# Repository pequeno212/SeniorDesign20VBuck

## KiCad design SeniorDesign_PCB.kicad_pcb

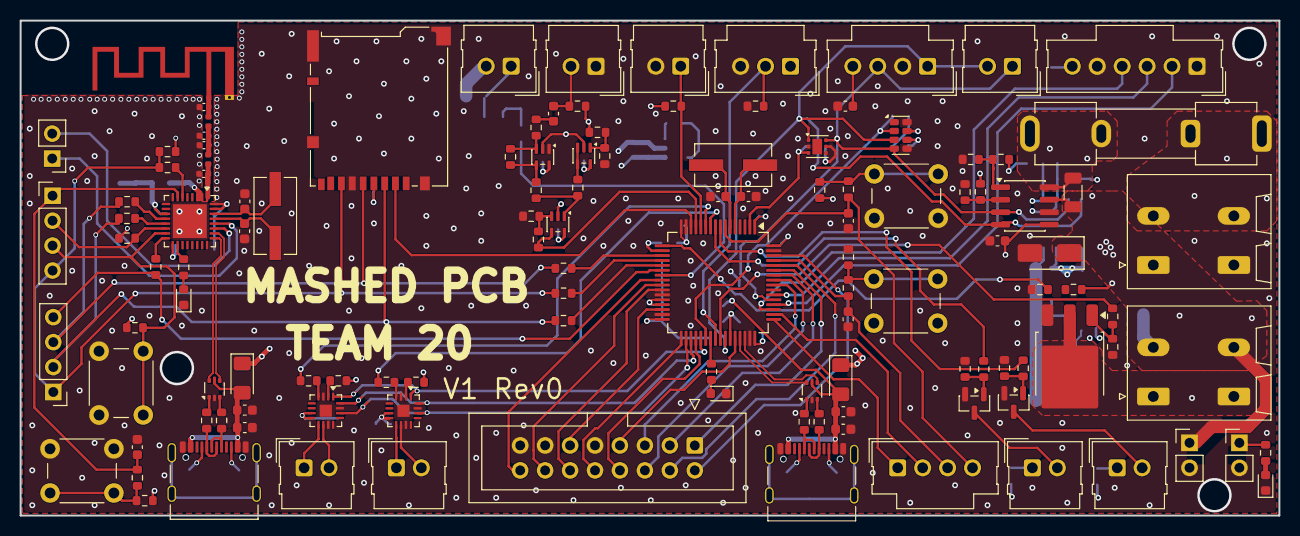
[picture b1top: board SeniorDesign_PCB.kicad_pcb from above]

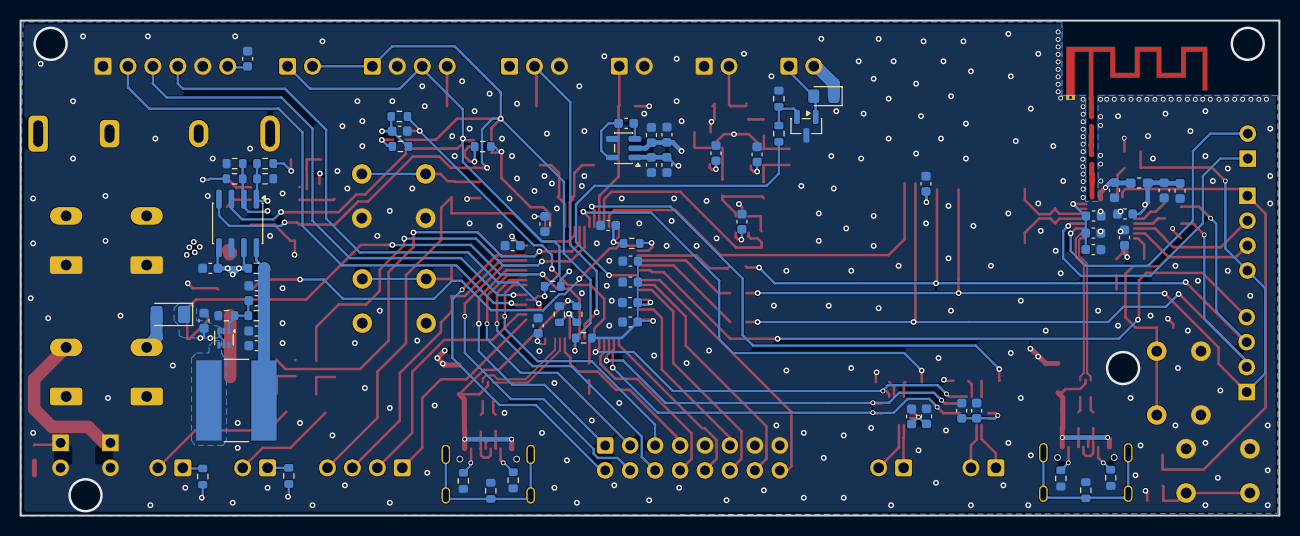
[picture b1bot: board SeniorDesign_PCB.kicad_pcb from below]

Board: 4 copper layers, 128.2 x 50.4 mm, 193 parts (70 on the bottom side), 135 nets.

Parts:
AE1: Antenna_Shield; Texas_SWRA117D_2.4GHz_Left
C1, C22, C23, C33, C39, C43, C48, C49: 1u; C_0603_1608Metric
C2, C3, C4, C5, C6, C7, C10, C11, C13, C14, C17, C18, C19, C24, C25, C32, C34, C35, C36, C37, C40, C41, C42, C44, C45, C46, C47, C50, C52, C53: 100n; C_0603_1608Metric
C8, C9, C26, C27: 22p; C_0603_1608Metric
C12, C16, C38: 10u; C_0603_1608Metric
C15: 1uF; C_0603_1608Metric
C20: 4u7; C_0603_1608Metric
C21: 22u; C_0603_1608Metric
C28, C29, C30, C31: DNP; C_0402_1005Metric
C51, C54, C55: DNP; C_0603_1608Metric
D2, D5, D9: LED; LED_0603_1608Metric
D4: SMAJ5.0A; D_SMA
D6, D7: D; D_1206_3216Metric_Pad1.42x1.75mm_HandSolder
D8: D; D_0805_2012Metric_Pad1.15x1.40mm_HandSolder
D10: D; D_1206_3216Metric
F1: RGEF1400; Fuseholder_Clip-5x20mm_Keystone_3512P_Inline_P23.62x7.27mm_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
J1, J4: Conn_01x04_Pin; Molex_SL_171971-0004_1x04_P2.54mm_Vertical
J2, J6, J7, J8, J19, J20: Conn_01x02_Socket; Molex_SL_171971-0002_1x02_P2.54mm_Vertical
J3: Conn_01x03_Socket; Molex_SL_171971-0003_1x03_P2.54mm_Vertical
J5, J15: Conn_01x02_Pin; Molex_SL_171971-0002_1x02_P2.54mm_Vertical
J10, J24: Conn_01x02_Socket; PhoenixContact_SPT_2.5_2-H-5.0_1x02_P5.0mm_Horizontal
J11: Conn_01x02_Pin; PinHeader_1x02_P2.54mm_Vertical
J12, J13: USB_C_Receptacle_USB2.0_14P; USB_C_Receptacle_Palconn_UTC16-G
J14: IDC_Cable_02x08; IDC-Header_2x08_P2.54mm_Vertical
J16, J17: Conn_01x04_Pin; PinHeader_1x04_P2.54mm_Vertical
J18: Micro_SD_Card; microSD_HC_Hirose_DM3BT-DSF-PEJS
J21: MIC_I2S_CONNECTOR; Molex_SL_171971-0006_1x06_P2.54mm_Vertical
J22, J23: Conn_01x02_Socket; PinHeader_1x02_P2.54mm_Vertical
L1: 1u; L_Bourns-SRN8040_8x8.15mm
L2, L3: DNP; L_0402_1005Metric
L4: 2n; L_0603_1608Metric_Pad1.05x0.95mm_HandSolder
Q1: NMOS; TO-252-3_TabPin2
Q2: NMOS; SOT-23
Q4, Q5: AO3400A; SOT-23
R2, R7, R8, R10, R15, R17, R18, R24, R25, R32, R38, R39, R53, R59, R60, R78, R79, R81, R84: 10k; R_0603_1608Metric
R3, R21: 2k2; R_0603_1608Metric
R5, R6, R44, R45, R46, R47: 5k1; R_0603_1608Metric
R9: 7k; R_0603_1608Metric
R11, R43, R54: 330; R_0603_1608Metric
R12, R13, R14, R20, R34, R35, R55, R56, R57, R58, R69, R70, R73, R75: 0R; R_0603_1608Metric
R19, R22, R26, R27, R28, R29, R37, R76: 1k; R_0603_1608Metric
R23: 18k; R_0603_1608Metric
R30: 210k; R_0603_1608Metric
R31, R52: 10R; R_0603_1608Metric
R33: 2m; R_1206_3216Metric
R36, R41: 100k; R_0603_1608Metric
R40: 453k; R_0603_1608Metric
R42: 2m; R_0603_1608Metric
R48, R49, R50, R51: 22R; R_0603_1608Metric
R61, R62, R68, R71, R72, R74: DNP; R_0603_1608Metric
R80, R83: 10; R_0603_1608Metric
R82, R85: 17; R_0603_1608Metric
SW2, SW5, SW6, SW7: SW_Push; SW_PUSH_6mm
U1: TMP117xxDRV; WSON-6-1EP_2x2mm_P0.65mm_EP1x1.6mm
U2: RV-3028-C7; MicroCrystal_C7_SON-8_1.5x3.2mm_P0.9mm
U3: STM32G474RETx; LQFP-64_10x10mm_P0.5mm
U5, U8: MAX98357A; TQFN-16-1EP_3x3mm_P0.5mm_EP1.23x1.23mm
U6, U7, U16: TLV172IDCK; SOT-353_SC-70-5
U9, U10: INA219AxD; SOIC-8_3.9x4.9mm_P1.27mm
U11: TLV62569ADRL; SOT-563
U12, U13: USBLC6-2P6; SOT-666
U14: ESP32-C3FH4; QFN-32-1EP_5x5mm_P0.5mm_EP3.45x3.45mm
U15: TPS60400DBV; SOT-23-5
Y1: 16MHz; Crystal_SMD_ECS_CSM3X-2Pin_7.6x4.1mm
Y2: 40MHz; Crystal_SMD_ECS_CSM3X-2Pin_7.6x4.1mm

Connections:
3V3: C1.1, C2.1, C3.1, C4.1, C5.1, C6.1, C7.1, C10.1, C12.1, C13.1, C14.1, C16.1, C17.1, C18.1, C19.1, C32.1, C34.1, C35.1, C36.1, C37.1, C38.1, C39.1, C40.1, C41.1, C44.1, C46.1, C47.1, C48.1, C52.1, C53.1, J1.4, J3.1, J18.4 (VDD), J21.6, J22.1, L4.2, R2.1, R3.1, R5.2, R6.2, R7.1, R8.1, R15.1, R18.1, R21.1, R24.2, R34.1, R35.1, R42.2, R43.1, R59.1, R60.1, R68.2, R69.2, R72.2, R74.2, R78.1, R79.1, R82.1, R85.1, SW2.2, U1.5 (V+), U2.7 (VDD), U3.1 (VBAT), U3.16 (VDD), U3.28 (VREF+), U3.29 (VDDA), U3.32 (VDD), U3.48 (VDD), U3.64 (VDD), U5.7 (VDD), U5.8 (VDD), U6.5 (V+), U7.5 (V+), U8.7 (VDD), U8.8 (VDD), U9.5 (VS), U10.5 (VS), U10.7 (IN-), U14.11 (VDD3P3_RTC), U14.17 (VDD3P3_CPU), U14.31 (VDDA), U14.32 (VDDA), U15.2 (IN), U16.5 (V+)
5V: D4.1 (A1), D8.1 (K), D10.2 (A), J10.2, J15.2, J23.1, R33.2, R38.1, U9.7 (IN-)
-3V3: C49.1, C50.1, U6.2 (V-), U7.2 (V-), U15.1 (OUT), U16.2 (V-)
/Analog/I2S2_CK: U3.35 (PB13), U5.16 (BCLK), U8.16 (BCLK)
/Analog/I2S2_SD: U3.37 (PB15), U5.1 (DIN), U8.1 (DIN)
/Analog/I2S2_WS: U3.34 (PB12), U5.14 (LRCLK), U8.14 (LRCLK)
/Analog/LEFT_SD_MODE: R20.1, U3.11 (PC3)
/Analog/MIC: R29.1, U3.13 (PA1), U7.4
/Analog/RIGHT_SD_MODE: R30.1, U3.10 (PC2)
/ESP32C3/BOOT: J17.3, R79.2, SW7.1, U14.15 (GPIO9/BOOT)
/ESP32C3/ESP32_RST: C45.1, J17.1, R76.1, U14.7 (CHIP_EN)
/ESP32C3/ESP32_USB_D_N: U13.6 (I/O1), U14.25 (GPIO18/USB_D-)
/ESP32C3/ESP32_USB_D_P: U13.4 (I/O2), U14.26 (GPIO19/USB_D+)
/ESP32C3/GPIO8: J17.2, R59.2, U14.14 (GPIO8)
/ESP32C3/LNA_IN: C31.1, L3.2, U14.1 (LNA_IN)
/ESP32C3/L_to_L: C29.1, C30.1, L2.2, L3.1
/ESP32C3/RF_ANT: AE1.1 (A), C28.1, L2.1
/ESP32C3/SPI1_CS_ESP: J16.4, R58.2, U3.22 (PC4)
/ESP32C3/SPI1_MISO: J16.1, J17.4, J18.7 (DAT0), R13.2, R57.2, R60.2
/ESP32C3/SPI1_MOSI: J16.2, J18.3 (CMD), R12.2, R56.1
/ESP32C3/SPI1_SCLK: J16.3, J18.5 (CLK), R14.2, R55.1
/ESP32C3/TEST_LED: R54.1, U14.18 (GPIO11)
/ESP32C3/UART_RX: J11.2, U14.27 (GPIO20)
/ESP32C3/UART_TX: J11.1, U14.28 (GPIO21)
/ESP32C3/XTAL_N: C26.1, U14.29 (XTAL_N), Y2.2
/ESP32C3/XTAL_P: C27.1, U14.30 (XTAL_P), Y2.1
/Peripherials/FAN_PWM: R52.2, U3.23 (PC5)
/Peripherials/INT_RTC: R8.2, U2.2 (~INT), U3.38 (PC6)
/Peripherials/MATRIX_A: J14.5, U3.56 (PB3)
/Peripherials/MATRIX_B: J14.12, U3.26 (PB2)
/Peripherials/MATRIX_B1: J14.2, U3.62 (PB9)
/Peripherials/MATRIX_B2: J14.4, U3.60 (PB7)
/Peripherials/MATRIX_C: J14.6, U3.57 (PB4)
/Peripherials/MATRIX_CLK: J14.7, U3.44 (PA10)
/Peripherials/MATRIX_D: J14.11, U3.30 (PB10)
/Peripherials/MATRIX_G1: J14.16, U3.24 (PB0)
/Peripherials/MATRIX_G2: J14.14, U3.25 (PB1)
/Peripherials/MATRIX_LAT: J14.10, U3.33 (PB11)
/Peripherials/MATRIX_OE: J14.8, U3.36 (PB14)
/Peripherials/MATRIX_R1: J14.1, U3.59 (PB6)
/Peripherials/MATRIX_R2: J14.3, U3.58 (PB5)
/Peripherials/SPI_CS_SD_CARD: J18.2 (DAT3/CD), U3.14 (PA2)
/Peripherials/STM32_USB_D_N: U3.45 (PA11), U12.6 (I/O1)
/Peripherials/STM32_USB_D_P: U3.46 (PA12), U12.4 (I/O2)
/Peripherials/USB_N_ESP_ESD: R50.2, U13.1 (I/O1)
/Peripherials/USB_N_ESP_RES: J13.A7 (D-), J13.B7 (D-), R50.1
/Peripherials/USB_N_STM_ESD: R48.2, U12.1 (I/O1)
/Peripherials/USB_N_STM_RES: J12.A7 (D-), J12.B7 (D-), R48.1
/Peripherials/USB_P_ESP_ESD: R51.2, U13.3 (I/O2)
/Peripherials/USB_P_ESP_RES: J13.A6 (D+), J13.B6 (D+), R51.1
/Peripherials/USB_P_STM_ESD: R49.2, U12.3 (I/O2)
/Peripherials/USB_P_STM_RES: J12.A6 (D+), J12.B6 (D+), R49.1
/Peripherials/VBUS_ESP: C23.1, C25.1, D6.2 (A), J13.A4 (VBUS), J13.A9 (VBUS), J13.B4 (VBUS), J13.B9 (VBUS), U13.5 (VBUS)
/Peripherials/VBUS_STM: C22.1, C24.1, D7.2 (A), J12.A4 (VBUS), J12.A9 (VBUS), J12.B4 (VBUS), J12.B9 (VBUS), R9.1, U12.5 (VBUS)
/Power/3V3_AMPS_1: C21.1, C51.1, C54.1, C55.1, L1.2, R40.1, R42.1, U10.8 (IN+)
/Power/5V_AMPS_1: F1.2, R33.1, U9.8 (IN+)
/Power/5V_VOLTS: R38.2, R39.1, U3.17 (PA3)
/Power/I2C3_SCL: J1.1, J5.2, R5.1, U1.1 (SCL), U2.3 (SCL), U3.42 (PA8), U9.4 (SCL), U10.4 (SCL)
/Power/I2C3_SDA: J1.3, J5.1, R6.1, U1.6 (SDA), U2.4 (SDA), U3.53 (PC11), U9.3 (SDA), U10.3 (SDA)
/Power/MATRIX_PWR_EN: R31.1, U3.41 (PC9)
/STM32G4/3V3_VOLTS: R15.2, U3.18 (PA4)
/STM32G4/ALS_ADC: J2.1, R3.2, U3.12 (PA0)
/STM32G4/BOOT0: C11.1, J4.3, R19.1, U3.61 (PB8)
/STM32G4/CLK_IN: C8.1, U3.5 (PF0), Y1.2
/STM32G4/CLK_OUT: C9.1, U3.6 (PF1), Y1.1
/STM32G4/I2S3_CK: J21.2, U3.52 (PC10)
/STM32G4/I2S3_SD: J21.3, U3.54 (PC12)
/STM32G4/I2S3_WS: J21.4, U3.51 (PA15)
/STM32G4/INT_TEMP_ALERT: R2.2, U1.3 (ALERT), U3.2 (PC13)
/STM32G4/PAPIR: J3.2, R36.1, U3.40 (PC8)
/STM32G4/SPI1_MISO_0: R13.1, U3.20 (PA6)
/STM32G4/SPI1_MOSI_0: R12.1, U3.21 (PA7)
/STM32G4/SPI1_SCLK_0: R14.1, U3.19 (PA5)
/STM32G4/SWDCLK: J4.2, U3.50 (PA14)
/STM32G4/SWDIO: J4.1, U3.49 (PA13)
/STM32G4/TEST_LED: R11.1, U3.39 (PC7)
/STM32G4/TV_IR_PWM_1: R80.2, U3.8 (PC0)
/STM32G4/TV_IR_PWM_2: R83.2, U3.9 (PC1)
/STM32G4/USB_VBUS_DETECT: R9.2, R10.1, U3.43 (PA9)
/STM32G4/nRST: C42.1, J4.4, R37.1, U3.7 (PG10)
GND: AE1.2 (Shield), C1.2, C2.2, C3.2, C4.2, C5.2, C6.2, C7.2, C8.2, C9.2, C10.2, C11.2, C12.2, C13.2, C14.2, C16.2, C17.2, C18.2, C19.2, C20.2, C21.2, C22.2, C23.2, C24.2, C25.2, C26.2, C27.2, C28.2, C29.2, C30.2, C31.2, C32.2, C33.2, C34.2, C35.2, C36.2, C37.2, C38.2, C39.2, C40.2, C41.2, C42.2, C44.2, C45.2, C46.2, C47.2, C48.2, C49.2, C50.2, C52.2, C53.2, C54.2, C55.2, D2.1 (K), D4.2 (A2), D5.1 (K), D9.1 (K), J1.2, J2.2, J3.3, J6.1, J12.A1 (GND), J12.A12 (GND), J12.B1 (GND), J12.B12 (GND), J13.A1 (GND), J13.A12 (GND), J13.B1 (GND), J13.B12 (GND), J14.9, J14.13, J14.15, J18.6 (VSS), J18.SH (SHIELD), J21.1, J21.5, J22.2, J23.2, J24.1, Q1.3 (S), Q2.3 (S), Q4.2 (S), Q5.2 (S), R10.2, R17.2, R25.1, R28.1, R32.2, R36.2, R39.2, R41.2, R44.1, R45.1, R46.1, R47.1, R53.1, R61.1, R62.1, R70.1, R71.1, R73.1, R75.1, R81.2, R84.2, SW5.2, SW6.2, SW7.2, U1.2 (GND), U1.4 (ADD0), U2.5 (VSS), U2.8 (EVI), U3.15 (VSS), U3.27 (VSSA), U3.31 (VSS), U3.47 (VSS), U3.63 (VSS), U5.3 (GND), U5.11 (GND), U5.15 (GND), U5.17 (PAD), U6.1 (+), U8.3 (GND), U8.11 (GND), U8.15 (GND), U8.17 (PAD), U9.6 (GND), U10.6 (GND), U11.2 (GND), U12.2 (GND), U13.2 (GND), U14.33 (GND), U15.4 (GND)
unnamed: C15.1, R22.1
unnamed: D2.2 (A), R11.2
unnamed: D5.2 (A), R43.2
unnamed: D8.2 (A), J15.1, Q2.1 (D)
unnamed: D9.2 (A), R54.2
unnamed: C15.2, J6.2, R21.2
unnamed: J7.1, U5.9 (OUTP)
unnamed: J7.2, U5.10 (OUTN)
unnamed: J8.1, U8.9 (OUTP)
unnamed: J8.2, U8.10 (OUTN)
unnamed: J10.1, Q1.2 (D)
unnamed: J12.A5 (CC1), R46.2
unnamed: J12.B5 (CC2), R44.2
unnamed: J12.SH (SHIELD), R61.2
unnamed: J13.A5 (CC1), R47.2
unnamed: J13.B5 (CC2), R45.2
unnamed: J13.SH (SHIELD), R62.2
unnamed: J19.1, R82.2
unnamed: J19.2, Q4.3 (D)
unnamed: J20.1, R85.2
unnamed: J20.2, Q5.3 (D)
unnamed: F1.1, J24.2
unnamed: Q1.1 (G), R31.2, R32.1
unnamed: Q2.2 (G), R52.1, R53.2
unnamed: Q4.1 (G), R80.1, R81.1
unnamed: Q5.1 (G), R83.1, R84.1
unnamed: R17.1, R19.2, SW2.1
unnamed: R18.2, R37.2, SW5.1
unnamed: R23.2, R27.1, U6.4
unnamed: R76.2, R78.2, SW6.1
unnamed: R7.2, U2.6 (VBACKUP)
unnamed: R35.2, U5.2 (GAIN_SLOT)
unnamed: R20.2, U5.4 (~SD_MODE)
unnamed: R22.2, R23.1, U6.3 (-)
unnamed: R26.2, R27.2, U7.1 (+)
unnamed: R28.2, R29.2, U7.3 (-)
unnamed: R34.2, U8.2 (GAIN_SLOT)
unnamed: R30.2, U8.4 (~SD_MODE)
unnamed: R68.1, R70.2, U9.2 (A0)
unnamed: R69.1, R71.2, U9.1 (A1)
unnamed: R72.1, R73.2, U10.2 (A0)
unnamed: R74.1, R75.2, U10.1 (A1)
unnamed: C51.2, R40.2, R41.1, U11.1 (FB)
unnamed: L1.1, U11.4 (SW)
unnamed: R57.1, U14.6 (GPIO2)
unnamed: R55.2, U14.12 (GPIO6)
unnamed: R56.2, U14.13 (GPIO7)
unnamed: R58.1, U14.16 (GPIO10)
unnamed: C43.1, U15.5 (C_{FLY+})
unnamed: C43.2, U15.3 (C_{FLY-})
unnamed: R24.1, R25.2, U16.1 (+)
unnamed: R26.1, U16.3 (-), U16.4
USB_5V: C20.1, D6.1 (K), D7.1 (K), D10.1 (K), U11.3 (VIN), U11.5 (EN)
VDD3P3: C33.1, L4.1, U14.2 (VDD3P3), U14.3 (VDD3P3)
